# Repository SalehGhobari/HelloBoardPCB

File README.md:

# HelloBoardPCB
Kicad PCB design of my first ever MCU pcb

# Current Schematic

# Current Layout

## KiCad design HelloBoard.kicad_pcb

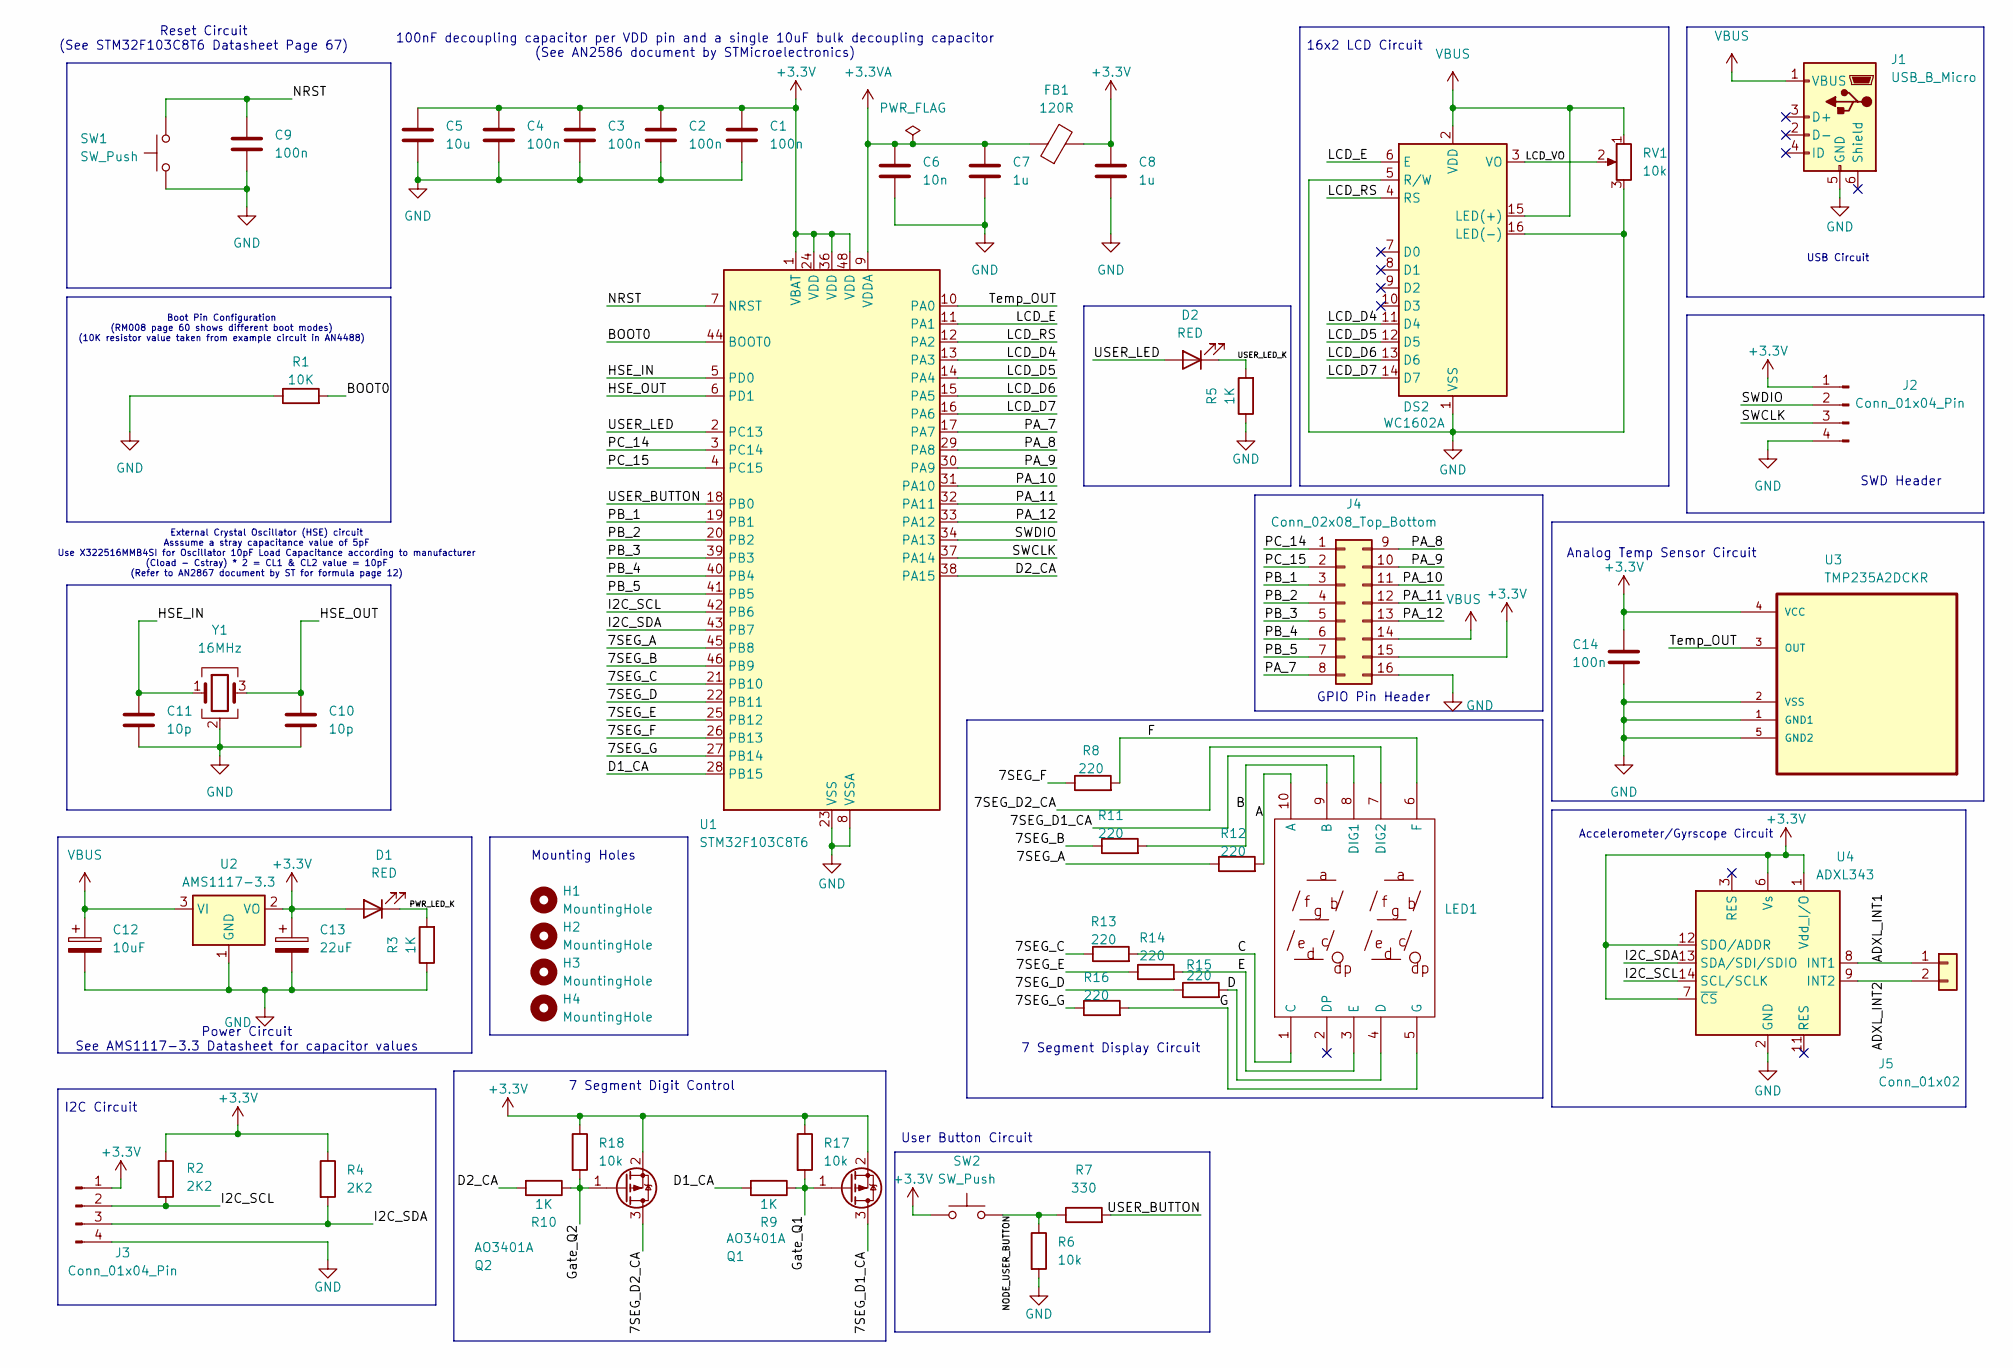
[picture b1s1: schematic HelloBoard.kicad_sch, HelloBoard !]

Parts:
C1, C2, C3, C4, C9, C14: 100n; C_0402_1005Metric
C5: 10u; C_0603_1608Metric
C6: 10n; C_0402_1005Metric
C7, C8: 1u; C_0402_1005Metric
C10, C11: 10p; C_0402_1005Metric
C12: 10uF; CP_EIA-3528-21_Kemet-B
C13: 22uF; CP_EIA-3528-21_Kemet-B
D1, D2: RED; LED_0603_1608Metric
DS2: WC1602A
FB1: 120R; L_0603_1608Metric
H1, H2, H3, H4: MountingHole; MountingHole_2.2mm_M2
J1: USB_B_Micro; USB_Micro-B_Wuerth_629105150521
J2, J3: Conn_01x04_Pin; PinHeader_1x04_P2.54mm_Vertical
J4: Conn_02x08_Top_Bottom; PinHeader_2x08_P2.54mm_Vertical
J5: Conn_01x02; PinHeader_1x02_P2.54mm_Vertical
LED1: 7Segment2Digit; Manufacturer Part SN460561N/0.56寸/共阴/2位; LCSC Part Name 2位0.56英寸红色数码管 共阴极
Q1, Q2: AO3401A; SOT-23
R1: 10K; R_0603_1608Metric
R2, R4: 2K2; R_0603_1608Metric
R3, R5, R9, R10: 1K; R_0603_1608Metric
R6, R17, R18: 10k; R_0603_1608Metric
R7: 330; R_0402_1005Metric
R8, R11, R12, R13, R14, R15, R16: 220; R_0402_1005Metric
RV1: 10k; Potentiometer_Bourns_3296W_Vertical
SW1, SW2: SW_Push; SW_PUSH_6mm_H5mm
U1: STM32F103C8T6; LQFP-48_7x7mm_P0.5mm
U2: AMS1117-3.3; SOT-223-3_TabPin2
U3: TMP235A2DCKR; SOT65P210X110-5N
U4: ADXL343; LGA-14_3x5mm_P0.8mm_LayoutBorder1x6y
Y1: 16MHz; Crystal_SMD_3225-4Pin_3.2x2.5mm

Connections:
+3.3V: C1.1, C2.1, C3.1, C4.1, C5.1, C8.1, C13.1, C14.1, D1.2 (A), FB1.2, J2.1, J3.1, J4.15, Q1.2 (S), Q2.2 (S), R2.1, R4.1, R17.1, R18.1, SW2.1, U1.1 (VBAT), U1.24 (VDD), U1.36 (VDD), U1.48 (VDD), U2.2 (VO), U3.4 (VCC), U4.1 (Vdd_I/O), U4.6 (Vs), U4.7 (~CS), U4.12 (SDO/ADDR)
+3.3VA: C6.1, C7.1, FB1.1, U1.9 (VDDA)
/7SEG_A: R12.1, U1.45 (PB8)
/7SEG_B: R11.1, U1.46 (PB9)
/7SEG_C: R13.1, U1.21 (PB10)
/7SEG_D: R15.1, U1.22 (PB11)
/7SEG_D1_CA: LED1.8 (DIG1), Q1.3 (D)
/7SEG_D2_CA: LED1.7 (DIG2), Q2.3 (D)
/7SEG_E: R14.1, U1.25 (PB12)
/7SEG_F: R8.1, U1.26 (PB13)
/7SEG_G: R16.1, U1.27 (PB14)
/A: LED1.10 (A), R12.2
/ADXL_INT1: J5.1, U4.8 (INT1)
/ADXL_INT2: J5.2, U4.9 (INT2)
/B: LED1.9 (B), R11.2
/BOOT0: R1.2, U1.44 (BOOT0)
/C: LED1.1 (C), R13.2
/D: LED1.4 (D), R15.2
/D1_CA: R9.2, U1.28 (PB15)
/D2_CA: R10.2, U1.38 (PA15)
/E: LED1.3 (E), R14.2
/F: LED1.6 (F), R8.2
/G: LED1.5 (G), R16.2
/Gate_Q1: Q1.1 (G), R9.1, R17.2
/Gate_Q2: Q2.1 (G), R10.1, R18.2
/HSE_IN: C11.1, U1.5 (PD0), Y1.1
/HSE_OUT: C10.1, U1.6 (PD1), Y1.3
/I2C_SCL: J3.2, R2.2, U1.42 (PB6), U4.14 (SCL/SCLK)
/I2C_SDA: J3.3, R4.2, U1.43 (PB7), U4.13 (SDA/SDI/SDIO)
/LCD_D4: DS2.11 (D4), U1.13 (PA3)
/LCD_D5: DS2.12 (D5), U1.14 (PA4)
/LCD_D6: DS2.13 (D6), U1.15 (PA5)
/LCD_D7: DS2.14 (D7), U1.16 (PA6)
/LCD_E: DS2.6 (E), U1.11 (PA1)
/LCD_RS: DS2.4 (RS), U1.12 (PA2)
/LCD_VO: DS2.3 (VO), RV1.2
/NODE_USER_BUTTON: R6.1, R7.1, SW2.2
/NRST: C9.1, SW1.2, U1.7 (NRST)
/PA_7: J4.8, U1.17 (PA7)
/PA_8: J4.9, U1.29 (PA8)
/PA_9: J4.10, U1.30 (PA9)
/PA_10: J4.11, U1.31 (PA10)
/PA_11: J4.12, U1.32 (PA11)
/PA_12: J4.13, U1.33 (PA12)
/PB_1: J4.3, U1.19 (PB1)
/PB_2: J4.4, U1.20 (PB2)
/PB_3: J4.5, U1.39 (PB3)
/PB_4: J4.6, U1.40 (PB4)
/PB_5: J4.7, U1.41 (PB5)
/PC_14: J4.1, U1.3 (PC14)
/PC_15: J4.2, U1.4 (PC15)
/PWR_LED_K: D1.1 (K), R3.2
/SWCLK: J2.3, U1.37 (PA14)
/SWDIO: J2.2, U1.34 (PA13)
/Temp_OUT: U1.10 (PA0), U3.3 (OUT)
/USER_BUTTON: R7.2, U1.18 (PB0)
/USER_LED: D2.2 (A), U1.2 (PC13)
/USER_LED_K: D2.1 (K), R5.2
GND: C1.2, C2.2, C3.2, C4.2, C5.2, C6.2, C7.2, C8.2, C9.2, C10.2, C11.2, C12.2, C13.2, C14.2, DS2.1 (VSS), DS2.5 (R/W), DS2.16 (LED(-)), J1.5 (GND), J2.4, J3.4, J4.16, R1.1, R3.1, R5.1, R6.2, RV1.3, SW1.1, U1.8 (VSSA), U1.23 (VSS), U1.35 (VSS), U1.47 (VSS), U2.1 (GND), U3.1 (GND1), U3.2 (VSS), U3.5 (GND2), U4.2 (GND), U4.4 (GND), U4.5 (GND), Y1.2 (G), Y1.4 (G)
VBUS: C12.1, DS2.2 (VDD), DS2.15 (LED(+)), J1.1 (VBUS), J4.14, RV1.1, U2.3 (VI)

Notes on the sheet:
Power Circuit See AMS1117-3.3 Datasheet for capacitor values
Reset Circuit (See STM32F103C8T6 Datasheet Page 67)
External Crystal Oscillator (HSE) circuit Asssume a stray capacitance value of 5pF Use X322516MMB4SI for Oscillator 10pF Load Capacitance according to manufacturer (Cload - Cstray) * 2 = CL1 & CL2 value = 10pF (Refer to AN2867 document by ST for formula page 12)
USB Circuit
Mounting Holes
16x2 LCD Circuit
User Button Circuit
Accelerometer/Gyrscope Circuit
100nF decoupling capacitor per VDD pin and a single 10uF bulk decoupling capacitor (See AN2586 document by STMicroelectronics)
SWD Header
7 Segment Display Circuit
GPIO Pin Header
7 Segment Digit Control
Boot Pin Configuration (RM008 page 60 shows different boot modes) (10K resistor value taken from example circuit in AN4488)
Analog Temp Sensor Circuit
I2C Circuit

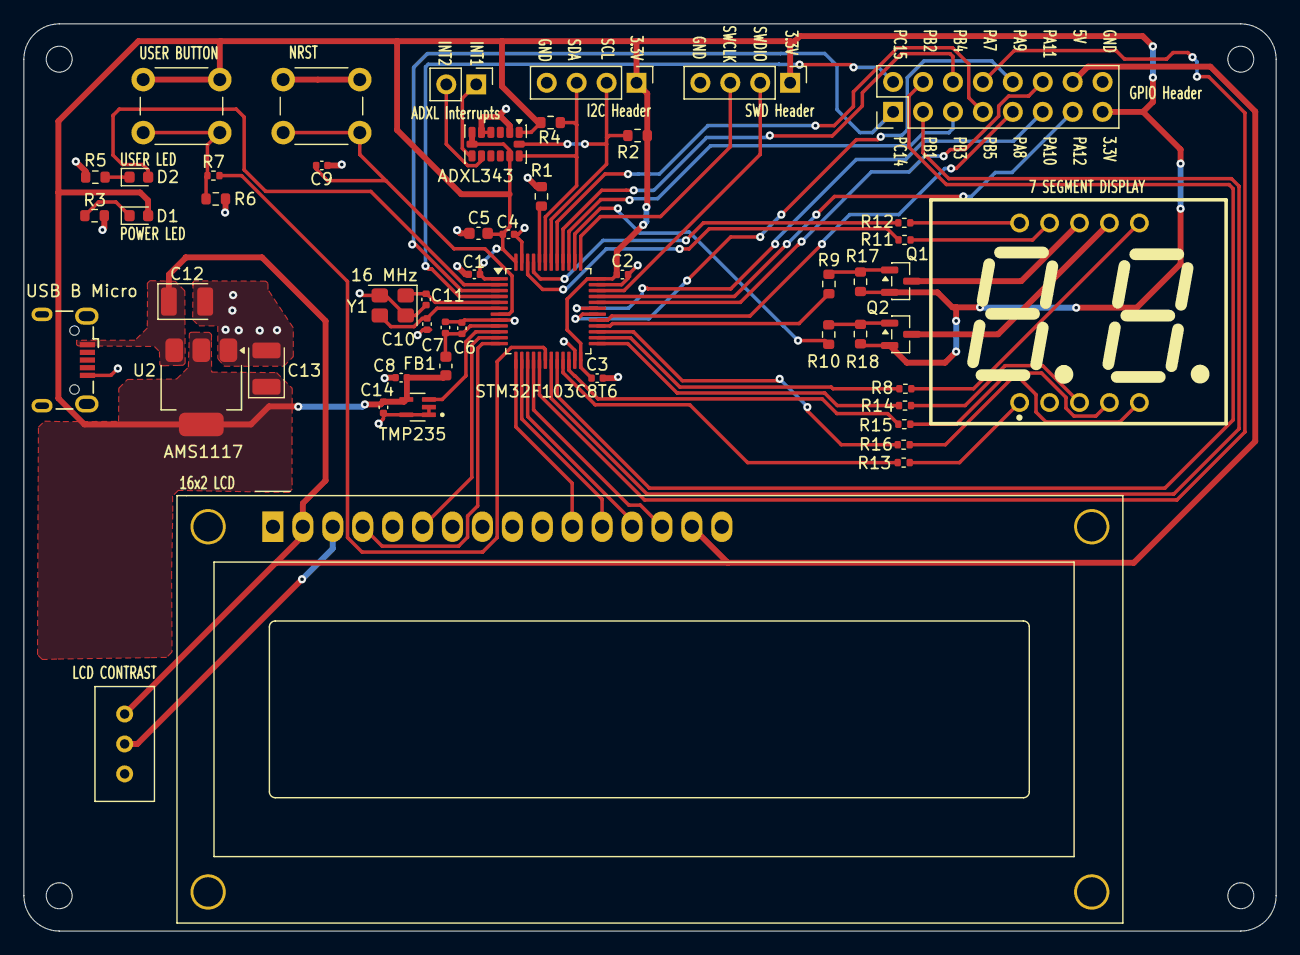
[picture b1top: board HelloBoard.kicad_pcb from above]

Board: 2 copper layers, 106.3 x 77.0 mm, 56 parts (0 on the bottom side), 60 nets.

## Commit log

2026-03-04 empty project
2026-03-05 Added Power, I2C, BOOT0, NRST, HSE, USB, SWD, TempSensor
2026-03-06 added user push button, user LED, 4 digit 7 segment ?
2026-03-06 image for README
2026-03-06 README edit
2026-03-07 added 16x2 LCD
2026-03-07 Finished Schematic (for now)
2026-03-08 Added footprints for layout
2026-03-17 added SilkScreen images and external pulldown for user button
2026-03-25 swapped 7Seg footprint
2026-03-27 started rough layout
2026-03-27 basic placement done
2026-03-27 Remove accidental FETCH_HEAD file
2026-03-27 added ground plane
2026-03-31 added "power puddles" shoutout phil's lab
2026-04-01 حلتيته
2026-04-01 gonna try stuff, checkpoint
2026-04-01 about to run DRC
2026-04-01 the router ?
2026-04-01 board images
2026-04-02 minor silkscreen edits
2026-04-03 minor via edits
2026-04-04 stuck with the ams1117-3.3
2026-04-04 TODO 7segment digit control
2026-04-04 board finished (for now)
2026-04-04 minor silkscreen edit & board images
2026-04-06 edited project specific libs
2026-04-06 VBUS copper pour changed
2026-04-08 BOM preparation
2026-04-08 backside silkscreen added
2026-04-08 more backside silkscreen
